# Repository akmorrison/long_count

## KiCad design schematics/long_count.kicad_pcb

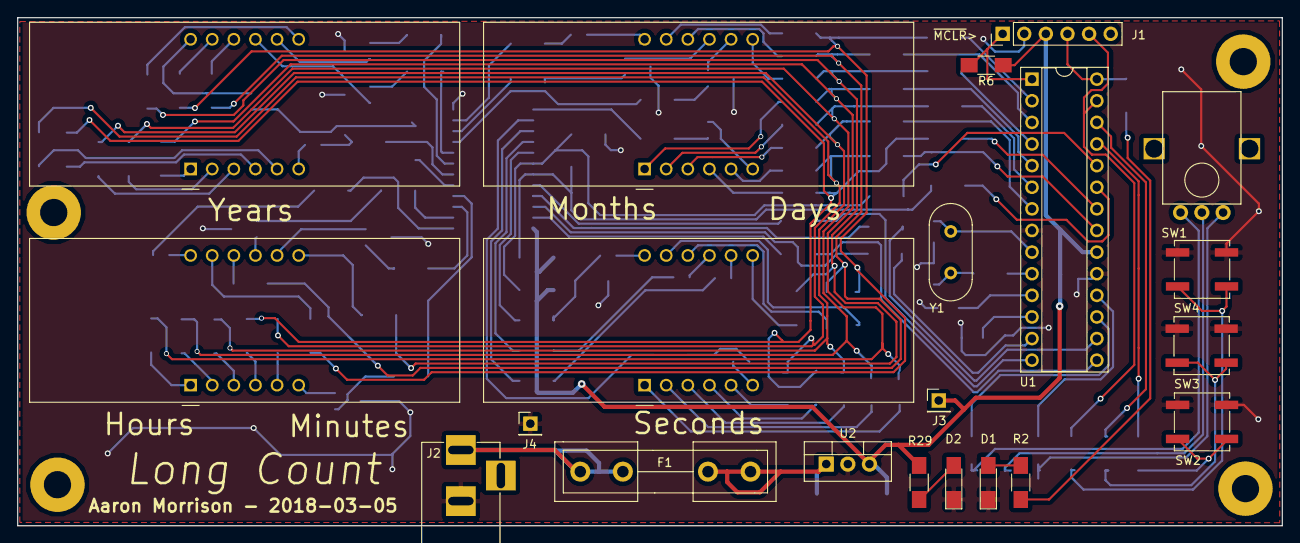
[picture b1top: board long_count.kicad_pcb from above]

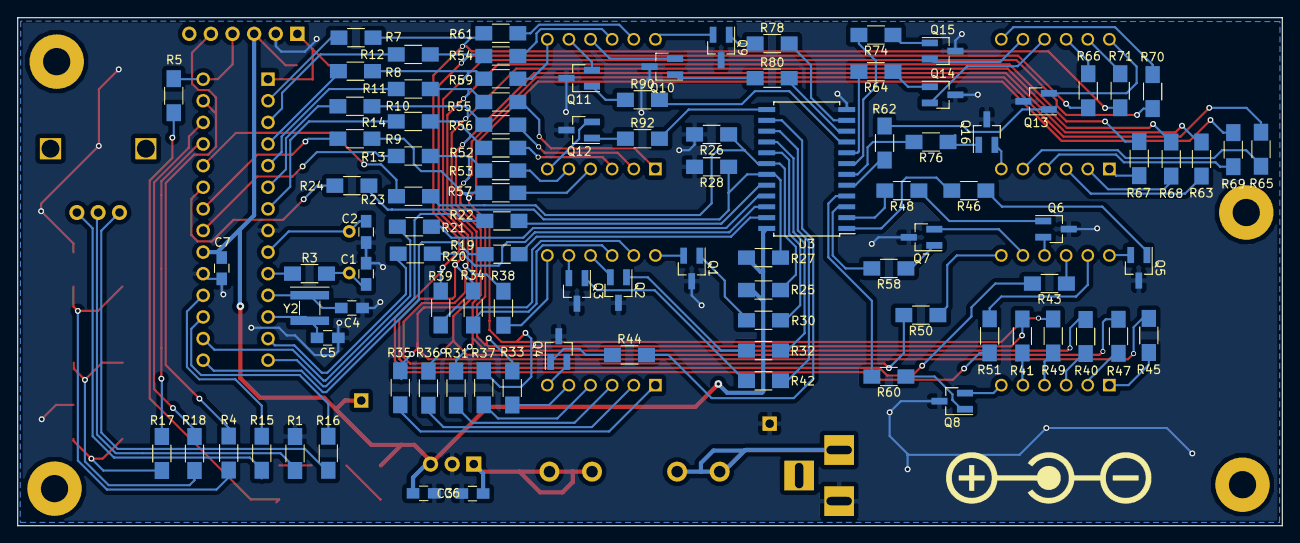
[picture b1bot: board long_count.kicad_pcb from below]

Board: 2 copper layers, 148.6 x 59.7 mm, 120 parts (99 on the bottom side), 133 nets.

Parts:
AFF1, AFF2, AFF3, AFF4: CC56-12; CA56-12SYKWA
C1, C2, C3, C4, C5, C6, C7: C; C_0805_HandSoldering
D1: STAT; LED_1206_HandSoldering
D2: PWR; LED_1206_HandSoldering
F1: Fuse; Fuseholder5x20_horiz_open_inline_Type-I
J1: PICKIT connector; Pin_Header_Straight_1x06_Pitch2.54mm
J2: BARREL_JACK
J3: VDD; Pin_Header_Straight_1x01_Pitch2.54mm
J4: VSS; Pin_Header_Straight_1x01_Pitch2.54mm
Q1, Q2, Q3, Q4, Q5, Q6, Q7, Q8, Q9, Q10, Q11, Q12, Q13, Q14, Q15, Q16: Q_PNP_BEC; SOT-23_Handsoldering
R1, R4, R5, R7, R8, R9, R10, R11, R12, R13, R14, R15, R16, R17, R18, R19, R20, R21, R22, R23, R24: 0; R_1206_HandSoldering
R2, R29, R31, R33, R34, R35, R36, R37, R38, R39, R40, R41, R43, R45, R47, R49, R50, R51, R52, R53, R54, R55, R56, R57, R59, R61, R63, R65, R66, R67, R68, R69, R70, R71: 330; R_1206_HandSoldering
R3: R; R_1206_HandSoldering
R6, R25, R26, R27, R28: 10k; R_1206_HandSoldering
R30, R32, R42, R44, R46, R48, R58, R60, R62, R64, R74, R76, R78, R80, R90, R92: 1K; R_1206_HandSoldering
SW1: Rotary_Encoder; rotary_encoder
SW2, SW3, SW4: SW_Push; SW_SPST_B3SL-1002P
U1: PIC18F27K40; DIP-28_W7.62mm_Socket
U2: LM7805CT; TO-220-3_Vertical
U3: CD74HC154M96; SOIC-24W_7.5x15.4mm_Pitch1.27mm
Y1: 12MHz; Crystal_HC49-4H_Vertical
Y2: 32.768KHz; Resonator_SMD_muRata_CDSCB-2pin_4.5x2.0mm_HandSoldering

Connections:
+5V: C6.2, C7.2, J1.3, J3.1, R6.1, R25.1, R27.1, R29.2, U1.20, U2.3, U3.24
/SevSeg2/DIG_1: R62.2, U3.5
/SevSeg2/DIG_2: R64.2, U3.8
/SevSeg2/DIG_3: R74.2, U3.7
/SevSeg2/DIG_4: R76.2, U3.6
/SevSeg3/DIG_1: R78.2, U3.11
/SevSeg3/DIG_2: R80.2, U3.10
/SevSeg3/DIG_3: R90.2, U3.9
/SevSeg3/DIG_4: R92.2, U3.13
/SevSeg4/DIG_1: R30.2, U3.17
/SevSeg4/DIG_2: R32.2, U3.16
/SevSeg4/DIG_3: R42.2, U3.15
/SevSeg4/DIG_4: R44.2, U3.14
/SevSeg/DIG_1: R46.2, U3.1
/SevSeg/DIG_2: R48.2, U3.2
/SevSeg/DIG_3: R58.2, U3.3
/SevSeg/DIG_4: R60.2, U3.4
GND: C1.2, C2.2, C3.1, C4.1, C5.1, C6.1, C7.1, D1.1, D2.1, J1.2, J2.2, J4.1, Q1.3, Q2.3, Q3.3, Q4.3, Q5.3, Q6.3, Q7.3, Q8.3, Q9.3, Q10.3, Q11.3, Q12.3, Q13.3, Q14.3, Q15.3, Q16.3, R1.1, R26.2, R28.2, SW2.1, SW3.1, SW4.1, U1.8, U1.19, U2.2, U3.12
ICSPCLK: J1.5, R4.1, U1.27
ICSPDAT: J1.4, R5.1, U1.28
unnamed: AFF1.1, R35.1
unnamed: AFF1.2, R36.1
unnamed: AFF1.3, R31.1
unnamed: AFF1.4, R37.1
unnamed: AFF1.5, R33.1
unnamed: AFF1.6, Q4.2
unnamed: AFF1.7, R38.1
unnamed: AFF1.8, Q3.2
unnamed: AFF1.9, Q2.2
unnamed: AFF1.10, R34.1
unnamed: AFF1.11, R39.1
unnamed: AFF1.12, Q1.2
unnamed: AFF2.1, R45.1
unnamed: AFF2.2, R47.1
unnamed: AFF2.3, R40.1
unnamed: AFF2.4, R49.1
unnamed: AFF2.5, R41.1
unnamed: AFF2.6, Q8.2
unnamed: AFF2.7, R50.1
unnamed: AFF2.8, Q7.2
unnamed: AFF2.9, Q6.2
unnamed: AFF2.10, R43.1
unnamed: AFF2.11, R51.1
unnamed: AFF2.12, Q5.2
unnamed: AFF3.1, R67.1
unnamed: AFF3.2, R68.1
unnamed: AFF3.3, R63.1
unnamed: AFF3.4, R69.1
unnamed: AFF3.5, R65.1
unnamed: AFF3.6, Q16.2
unnamed: AFF3.7, R70.1
unnamed: AFF3.8, Q15.2
unnamed: AFF3.9, Q14.2
unnamed: AFF3.10, R66.1
unnamed: AFF3.11, R71.1
unnamed: AFF3.12, Q13.2
unnamed: AFF4.1, R55.1
unnamed: AFF4.2, R56.1
unnamed: AFF4.3, R52.1
unnamed: AFF4.4, R57.1
unnamed: AFF4.5, R53.1
unnamed: AFF4.6, Q12.2
unnamed: AFF4.7, R59.1
unnamed: AFF4.8, Q11.2
unnamed: AFF4.9, Q10.2
unnamed: AFF4.10, R54.1
unnamed: AFF4.11, R61.1
unnamed: AFF4.12, Q9.2
unnamed: C1.1, R3.2, Y1.1
unnamed: C2.1, U1.9, Y1.2
unnamed: C3.2, F1.1, U2.1
unnamed: C4.2, U1.11, Y2.1
unnamed: C5.2, U1.12, Y2.2
unnamed: D1.2, R2.2
unnamed: D2.2, R29.1
unnamed: F1.2, J2.1
unnamed: Q1.1, R30.1
unnamed: Q2.1, R32.1
unnamed: Q3.1, R42.1
unnamed: Q4.1, R44.1
unnamed: Q5.1, R46.1
unnamed: Q6.1, R48.1
unnamed: Q7.1, R58.1
unnamed: Q8.1, R60.1
unnamed: Q9.1, R78.1
unnamed: Q10.1, R80.1
unnamed: Q11.1, R90.1
unnamed: Q12.1, R92.1
unnamed: Q13.1, R62.1
unnamed: Q14.1, R64.1
unnamed: Q15.1, R74.1
unnamed: Q16.1, R76.1
unnamed: R1.2, SW1.2
unnamed: R2.1, R5.2
unnamed: R3.1, U1.10
unnamed: R4.2, SW4.2
unnamed: R7.1, U1.2
unnamed: R8.1, U1.4
unnamed: R9.1, U1.22
unnamed: R10.1, U1.6
unnamed: R11.1, U1.5
unnamed: R12.1, U1.3
unnamed: R13.1, U1.21
unnamed: R14.1, U1.7
unnamed: R15.1, U1.18
unnamed: R15.2, SW1.3
unnamed: R16.1, U1.17
unnamed: R16.2, SW1.1
unnamed: R17.1, U1.25
unnamed: R17.2, SW2.2
unnamed: R18.1, U1.26
unnamed: R18.2, SW3.2
unnamed: R19.1, U3.23
unnamed: R19.2, U1.15
unnamed: R20.1, U3.22
unnamed: R20.2, U1.13
unnamed: R21.1, U3.21
unnamed: R21.2, U1.16
unnamed: R22.1, U3.20
unnamed: R22.2, U1.14
unnamed: R23.1, R25.2, R26.1, U3.18
unnamed: R23.2, U1.24
unnamed: R24.1, R27.2, R28.1, U3.19
unnamed: R24.2, U1.23
SEG_A: R7.2, R39.2, R51.2, R61.2, R71.2
SEG_B: R8.2, R38.2, R50.2, R59.2, R70.2
SEG_C: R9.2, R37.2, R49.2, R57.2, R69.2
SEG_D: R10.2, R36.2, R47.2, R56.2, R68.2
SEG_DP: R14.2, R31.2, R40.2, R52.2, R63.2
SEG_E: R11.2, R35.2, R45.2, R55.2, R67.2
SEG_F: R12.2, R34.2, R43.2, R54.2, R66.2
SEG_G: R13.2, R33.2, R41.2, R53.2, R65.2
~MCLR: J1.1, R6.2, U1.1

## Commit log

2018-03-05 Clean up schematic
    More readable, some notes on components and decisions, and a proper
    linear regulator. 7805 4lyfe.
2018-03-05 Add mounting holes
2018-03-05 Add silkscreen, move top left mounting hole so it's uncovered
2018-03-05 Change socket hole diameter to 1mm, instead of 0.8mm
2018-03-05 remove tracks through pads
2018-03-05 Generate gerbers
2018-03-05 Add test points for VDD and VSS
    Also add center positive polarity symbol for DC input
2018-03-05 Rename gerber files to a more standard naming convention
    Add DS_Store to gitignore because macs are weird
2018-03-09 Create a bom
2018-03-16 Initialize firmware project
2018-03-16 Add PIC datasheet link to bom
2018-03-16 Add empty sevensegment files
2018-06-30 Add seven segment display driver code
2018-06-30 Add configuration bits so it runs
2018-06-30 First workeable commit
    The number on the display counts up. Which is a start, I guess?
2018-07-01 It now counts up and down. So that's good
2018-07-02 Get rotary encoder working
    It counts up and down when you rotate it
2018-07-02 Add a basic editing mode
    A number blinks. rotary encoder increases or decreases that number.
    Buttons let you move the blinking number back and forth.
2018-07-04 uncategorized work, don't merge
